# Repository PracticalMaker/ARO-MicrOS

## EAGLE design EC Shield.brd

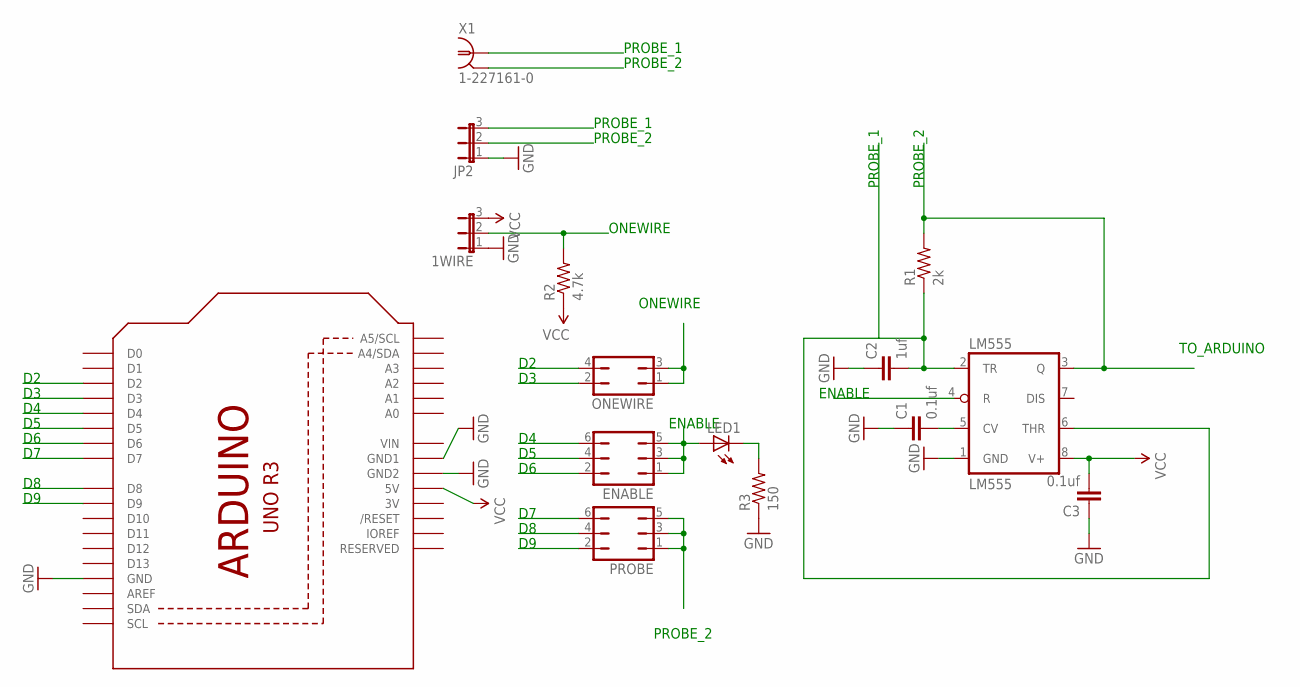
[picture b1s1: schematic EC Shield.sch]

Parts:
1WIRE: JP2E; JP2
C1, C3: 0.1uf; C0603
C2: 1uf; C0603
ENABLE: JP3Q
JP2: JP2E; JP2
LED1: LED0603; LED-0603
LM555: LM555; SO08
ONEWIRE: JP2Q
PROBE: JP3Q
R1: 2k; R0603
R2: 4.7k; R0603
R3: 150; R0603
U2: ARDUINOR3-DIMENSION; ARDUINOR3
X1: 1-227161-0; AMP_227161

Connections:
3V: U2.3V
D2: ONEWIRE.4, U2.D2
D3: ONEWIRE.2, U2.D3
D4: ENABLE.6, U2.D4
D5: ENABLE.4, U2.D5
D6: ENABLE.2, U2.D6
D7: PROBE.6, U2.D7
D8: PROBE.4, U2.D8
D9: PROBE.2, U2.D9
ENABLE: ENABLE.1, ENABLE.3, ENABLE.5, LED1.A, LM555.4 (R)
GND: 1WIRE.1, C1.1, C2.1, C3.1, JP2.1, LM555.1 (GND), R3.1, U2.GND, U2.GND1, U2.GND2
unnamed: C1.2, LM555.5 (CV)
unnamed: LED1.C, R3.2
ONEWIRE: 1WIRE.2, ONEWIRE.1, ONEWIRE.3, R2.2
PROBE_1: C2.2, JP2.3, LM555.2 (TR), LM555.6 (THR), R1.1, X1.1
PROBE_2: JP2.2, LM555.3 (Q), PROBE.1, PROBE.3, PROBE.5, R1.2, X1.2 (GND)
VCC: 1WIRE.3, C3.2, LM555.8 (V+), R2.1, U2.5V
VIN: U2.VIN

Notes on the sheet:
PROBE_1
PROBE_2
ONEWIRE
ENABLE
TO_ARDUINO

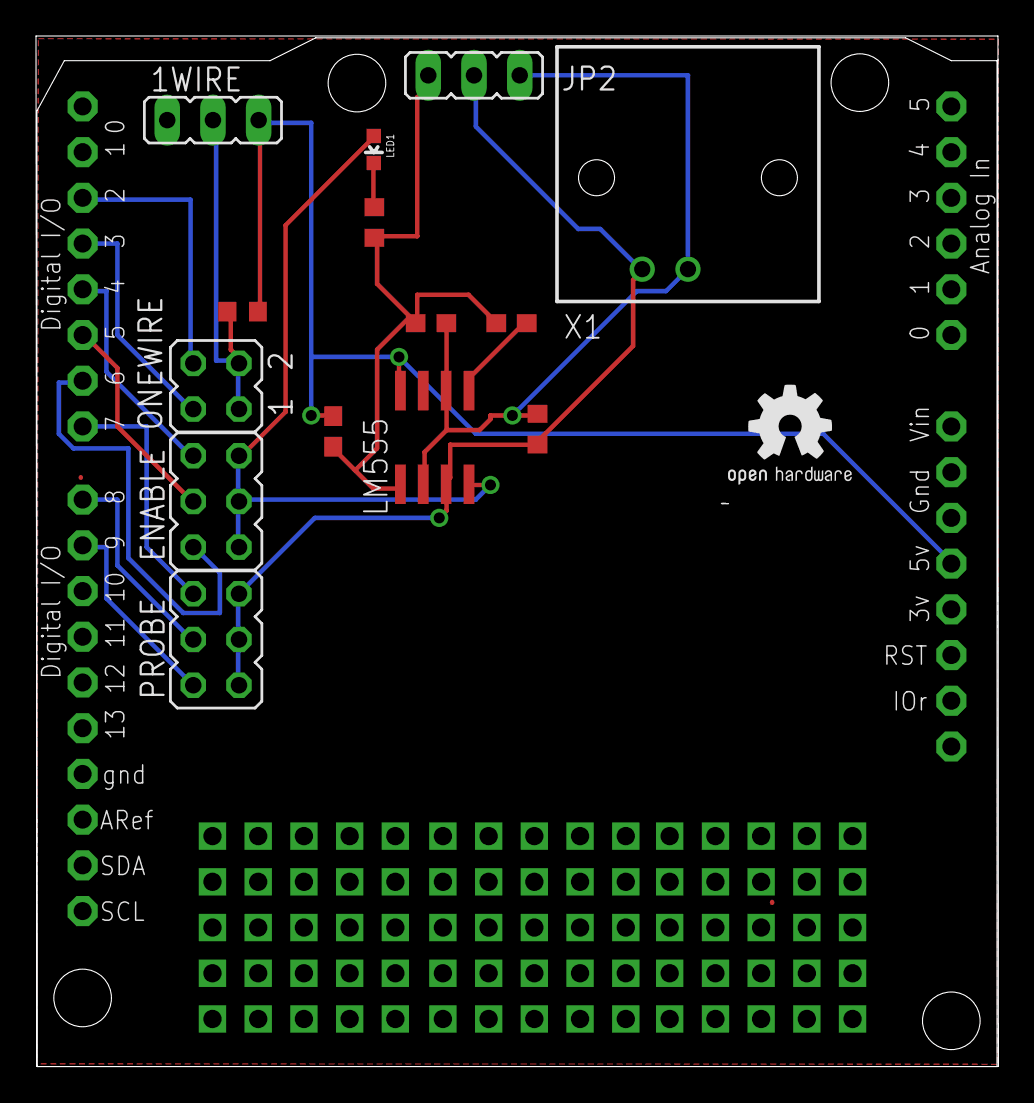
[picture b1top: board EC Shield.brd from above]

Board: 2 copper layers, 53.5 x 57.3 mm, 19 parts (0 on the bottom side), 16 nets.

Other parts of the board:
U$1: OSHW2
U$2, U$3, U$4: PROTO_VIAS_05X05

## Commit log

2011-06-06 import macroduino sketch
2011-06-06 libraries needed for sketch
2011-06-06 added in digital control via ethernet
2011-06-07 Edited MacroDuino.pde via GitHub
2011-06-08 rewrote interfaces and completed ethernet interface
2011-06-10 more manageable and ram usage improvements
2011-06-11 fixed ethernet and commands that were misnumbered
2011-06-11 fixing serial garbage output
2011-06-12 does jsonp callbacks
2011-06-14 fix serial interface problems
2011-06-20 #elseif error if CELSIUS was activated
2014-03-26 make into arduino library
2014-04-01 add readme
2014-04-04 add serial control demo
2014-04-04 uncomment debug serial
2014-10-30 readise working
